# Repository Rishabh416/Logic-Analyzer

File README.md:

I am currently taking apart a robot vacuum and a HP printer and to work on these projects I realised that I would need a logic analyzer to debug serial connections between different components
I researched and found a RPI Pico based firmware which can allow the microcontroller to serve as a multi channel logic analyzer hence decided to make a breakout board based around that.

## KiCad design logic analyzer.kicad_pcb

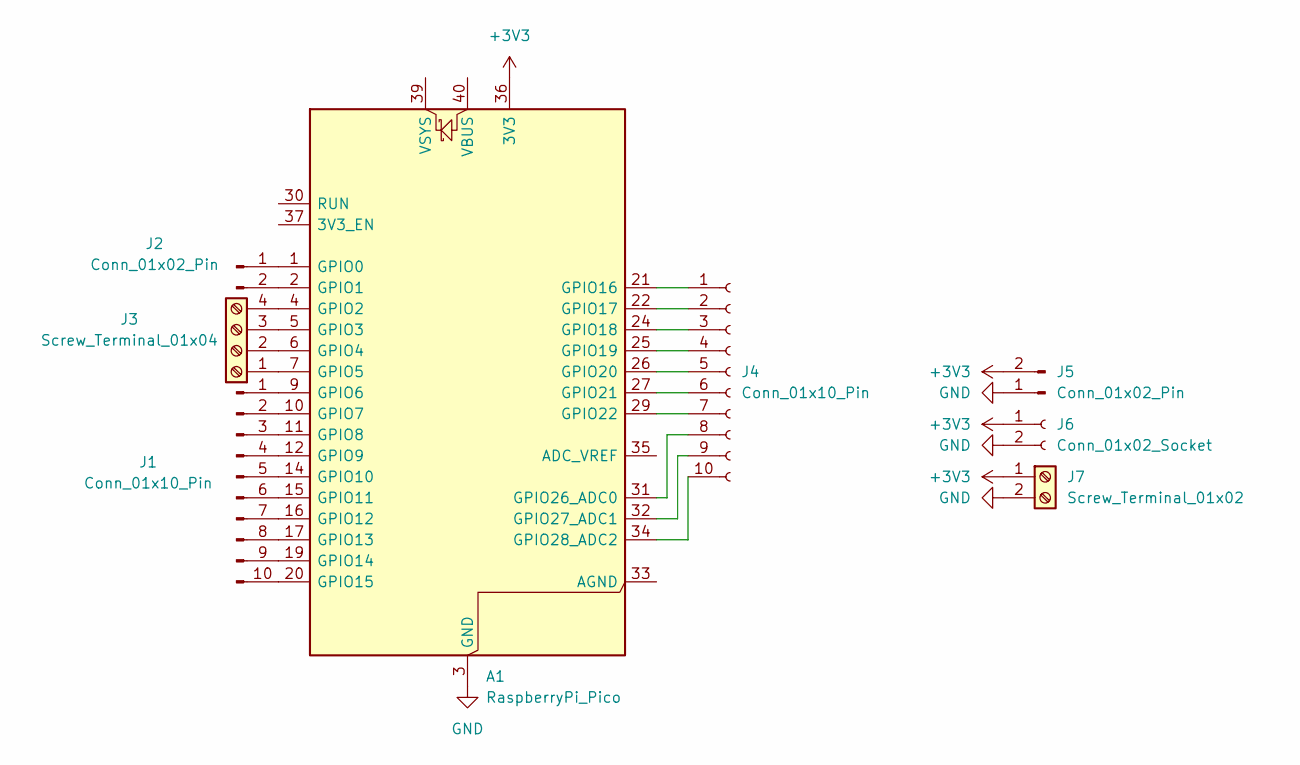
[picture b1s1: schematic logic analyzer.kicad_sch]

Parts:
A1: RaspberryPi_Pico; RaspberryPi_Pico_Common_THT
J1: Conn_01x10_Pin; PinHeader_1x10_P1.00mm_Vertical
J2, J5: Conn_01x02_Pin; PinHeader_1x02_P1.00mm_Vertical
J3: Screw_Terminal_01x04; TerminalBlock_Phoenix_MKDS-1,5-4_1x04_P5.00mm_Horizontal
J4: Conn_01x10_Pin; PinSocket_1x10_P1.00mm_Vertical
J6: Conn_01x02_Socket; PinSocket_1x02_P1.00mm_Vertical
J7: Screw_Terminal_01x02; TerminalBlock_Phoenix_MKDS-1,5-2-5.08_1x02_P5.08mm_Horizont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

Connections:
+3V3: A1.36 (3V3), J5.2, J6.1, J7.1
GND: A1.3 (GND), A1.8 (GND), A1.13 (GND), A1.18 (GND), A1.23 (GND), A1.28 (GND), A1.38 (GND), J5.1, J6.2, J7.2
unnamed: A1.1 (GPIO0), J2.1
unnamed: A1.2 (GPIO1), J2.2
unnamed: A1.4 (GPIO2), J3.4
unnamed: A1.5 (GPIO3), J3.3
unnamed: A1.6 (GPIO4), J3.2
unnamed: A1.7 (GPIO5), J3.1
unnamed: A1.9 (GPIO6), J1.1
unnamed: A1.10 (GPIO7), J1.2
unnamed: A1.11 (GPIO8), J1.3
unnamed: A1.12 (GPIO9), J1.4
unnamed: A1.14 (GPIO10), J1.5
unnamed: A1.15 (GPIO11), J1.6
unnamed: A1.16 (GPIO12), J1.7
unnamed: A1.17 (GPIO13), J1.8
unnamed: A1.19 (GPIO14), J1.9
unnamed: A1.20 (GPIO15), J1.10
unnamed: A1.21 (GPIO16), J4.1
unnamed: A1.22 (GPIO17), J4.2
unnamed: A1.24 (GPIO18), J4.3
unnamed: A1.25 (GPIO19), J4.4
unnamed: A1.26 (GPIO20), J4.5
unnamed: A1.27 (GPIO21), J4.6
unnamed: A1.29 (GPIO22), J4.7
unnamed: A1.31 (GPIO26_ADC0), J4.8
unnamed: A1.32 (GPIO27_ADC1), J4.9
unnamed: A1.34 (GPIO28_ADC2), J4.10

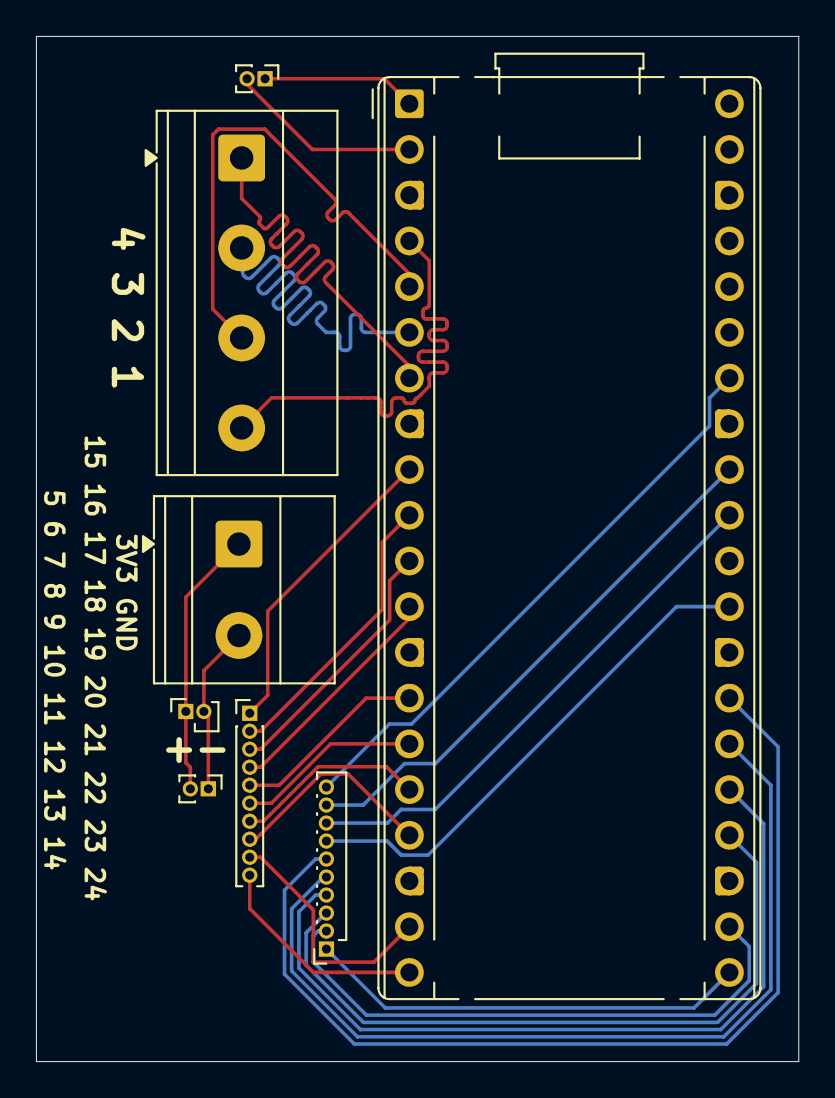
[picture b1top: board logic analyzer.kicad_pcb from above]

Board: 2 copper layers, 42.3 x 57.0 mm, 8 parts (0 on the bottom side), 28 nets.

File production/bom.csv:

Designator,Footprint,Quantity,Value,LCSC Part #
A1,RaspberryPi_Pico_Common_THT,1,RaspberryPi_Pico,
J1,PinHeader_1x10_P1.00mm_Vertical,1,Conn_01x10_Pin,
"J2, J5",PinHeader_1x02_P1.00mm_Vertical,2,Conn_01x02_Pin,
J3,"TerminalBlock_Phoenix_MKDS-1,5-4_1x04_P5.00mm_Horizontal",1,Screw_Terminal_01x04,
J4,PinSocket_1x10_P1.00mm_Vertical,1,Conn_01x10_Pin,
J6,PinSocket_1x02_P1.00mm_Vertical,1,Conn_01x02_Socket,
J7,"TerminalBlock_Phoenix_MKDS-1,5-2-5.08_1x02_P5.08mm_Horizontal",1,Screw_Terminal_01x02,

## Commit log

2026-06-22 Added README.md
2026-06-22 added production files
